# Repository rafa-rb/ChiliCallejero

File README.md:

# ChiliCallejero
Control tipo hitbox para Rasperry pi pico

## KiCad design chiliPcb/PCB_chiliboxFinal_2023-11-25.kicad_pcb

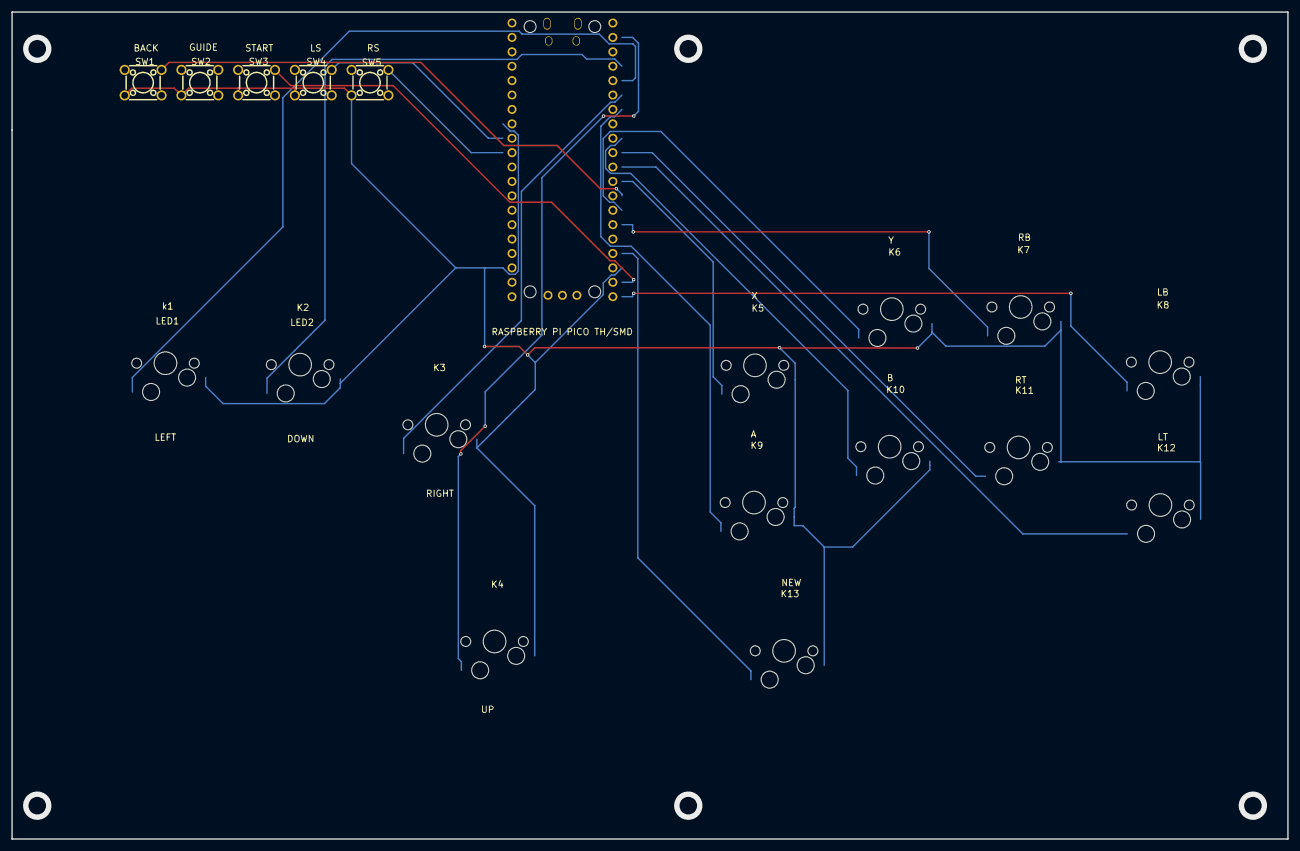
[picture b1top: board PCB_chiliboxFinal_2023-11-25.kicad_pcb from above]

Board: 2 copper layers, 225.0 x 145.8 mm, 19 parts (0 on the bottom side), 18 nets.

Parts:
K1, K2, K3, K4, K5, K6, K7, K8, K9, K10, K11, K12, K13: MXONLY-1U-HOTSWAP
SW1, SW2, SW3, SW4, SW5: TS-1095-A14B3-D1; SW-TH_4P-L6.0-W6.0-P4.50-LS6.5
U2: RASPBERRY PI PICO TH/SMD

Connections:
A: K9.2, U2.7
B: K10.2, U2.9
DOWN: K2.2, U2.4
GND: K1.1, K2.1, K3.1, K4.1, K5.1, K6.1, K7.1, K8.1, K9.1, K10.1, K11.1, K12.1, K13.1, SW1.3, SW2.3, SW3.3, SW4.3, SW5.3, U2.18, U2.23, U2.33
LB: K8.2, U2.20
LEFT: K1.2, U2.5
LS: SW4.2, U2.32
LT: K12.2, U2.11
NEW: K13.2, U2.17
RB: K7.2, U2.15
RIGHT: K3.2, U2.6
RS: SW5.2, U2.31
RT: K11.2, U2.10
SELECT: SW1.2, U2.13
START: SW3.2, U2.19
UP: K4.2, U2.2
X: K5.2, U2.12
Y: K6.2, U2.14
